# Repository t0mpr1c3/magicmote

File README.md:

Magic Mote
==========

Wireless sensor node interfacing low-power [MSP430G2553 microcontroller]("http://www.ti.com/product/msp430g2553") with [Nordic NRF24L01+]("https://www.sparkfun.com/datasheets/Components/SMD/nRF24L01Pluss_Preliminary_Product_Specification_v1_0.pdf") 2.4 GHz RF module.

Layout designed for easy compatibility with [msprf24]("https://github.com/spirilis/msprf24") and [Enrf24]("https://github.com/spirilis/Enrf24") libraries by Spirilis.

Blog post: [http://smokedprojects.blogspot.com/2017/03/magic-mote-msp430g2553-wireless-sensor.html](http://smokedprojects.blogspot.com/2017/03/magic-mote-msp430g2553-wireless-sensor.html)

Features
--------

* Unregulated power input from 2xAA or CR2032 Lithium coin cell
* 3.5mm jack socket/3 pin header with optional 2K2 pullup resistor on data line for 1-wire devices
* 4-pin header suitable for DHT22 temperature/humidity sensor
* Analogue input with low pass filter
* Tactile switch (can be mounted either side of board)
* Optional watch crystal
* Programming/serial header
* Dimensions suit panelization 24.5 x 49.00 mm footprint (2 panels on 5x5 cm)

Version history
---------------

_MO01_

First version.
Erratum: TXD and RXD labels permuted on 6-pin programming/serial header.

_MO02_

Switched TXD and RXD labels on 6-pin programming/serial header.
Moved from 3x8mm to 2x6mm watch crystal, with isolated ground plane, removed external capacitors.
Removed superfluous pulldown resistor on TST.
Changed programming/serial header to 2x3 footprint.
Changed switch to smaller SMD footprint and moved to more accessible position at side of board.

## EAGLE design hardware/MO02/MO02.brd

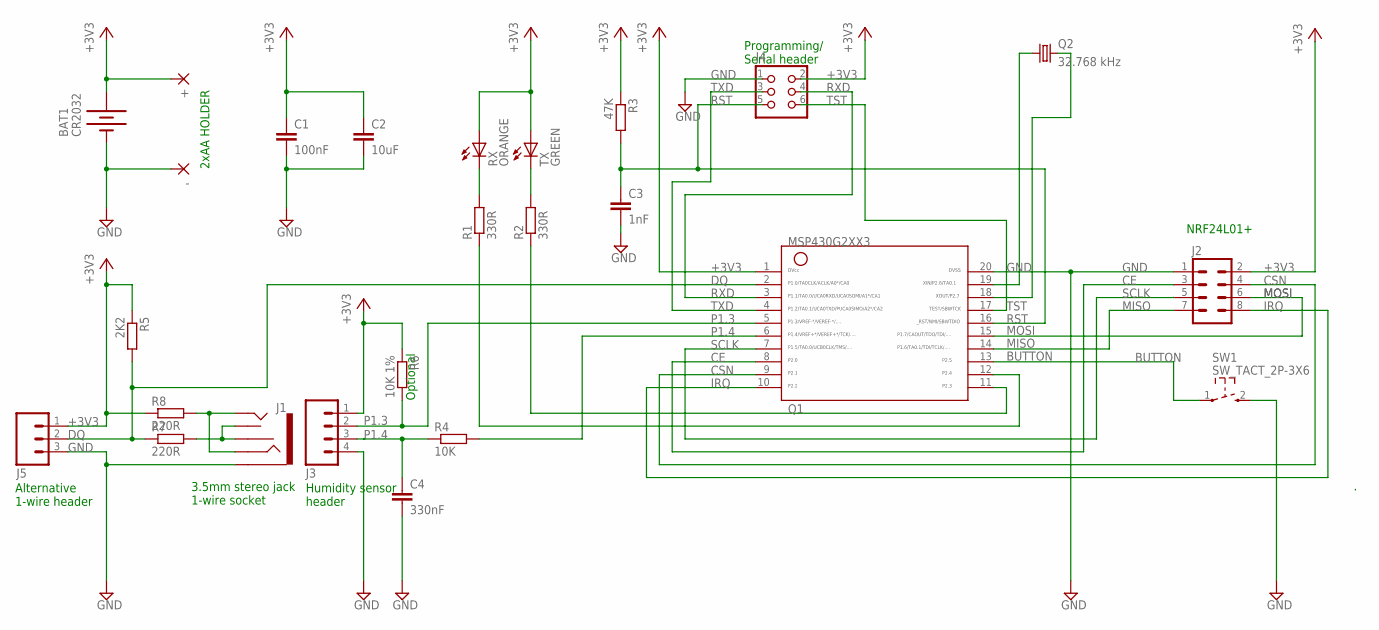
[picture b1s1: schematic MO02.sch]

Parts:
+: 2,54/1,0
-: 2,54/1,0
BAT1: CR2032; BATTCOM_20MM_PTH
C1: 100nF; C0805
C2: 10uF; C1206
C3: 1nF; C0805
C4: 330nF; C0805
J1: AUDIO-JACK2PTH; AUDIO-JACK
J2: M04X2; 2X4
J3: M04PTH; 1X04
J4: CON_HEADER_2X03-PTH; M2X3
J5: M03PTH; 1X03
Q1: G2XX3---PW20; PW20
Q2: 32.768 kHz; TC26H
R1, R2: 330R; M0805
R3: 47K; M0805
R4: 10K; M0805
R5: 2K2; M0805
R6: 10K 1%; M0805
R7, R8: 220R; M0805
RX: ORANGE; CHIPLED_0805
SW1: SW_TACT_2P-3X6; SW_TACT_3X6
TX: GREEN; CHIPLED_0805

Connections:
+3V3: +.1, BAT1.1 (+), C1.1, C2.1, J2.2, J3.1, J4.2, J5.1, Q1.1, R3.1, R5.1, R6.1, R8.1, RX.A, TX.A
BUTTON: Q1.13, SW1.1
CE: J2.3, Q1.8
CSN: J2.4, Q1.9
DQ: J5.2, Q1.2, R5.2, R7.1
GND: -.1, BAT1.2 (-), C1.2, C2.2, C3.2, C4.2, J1.SLEEVE, J2.1, J3.4, J4.1, J5.3, Q1.20, SW1.2 (3)
IRQ: J2.8, Q1.10
MISO: J2.7, Q1.14
MOSI: J2.6, Q1.15
unnamed: R2.2, TX.C
unnamed: R1.2, RX.C
unnamed: Q1.11, R2.1
unnamed: J1.RSH, J1.TSH, R7.2
unnamed: Q1.12, R1.1
unnamed: J1.RING, J1.TIP, R8.2
unnamed: C4.1, J3.3, R4.1
P1.3: J3.2, Q1.5, R6.2
P1.4: Q1.6, R4.2
P2.6: Q1.19, Q2.1
P2.7: Q1.18, Q2.2
RST: C3.1, J4.5, Q1.16, R3.2
RXD: J4.4, Q1.3
SCLK: J2.5, Q1.7
TST: J4.6, Q1.17
TXD: J4.3, Q1.4

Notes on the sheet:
3.5mm stereo jack 1-wire socket
NRF24L01+
Programming/ Serial header
Alternative 1-wire header
Humidity sensor header
Optional
2xAA HOLDER

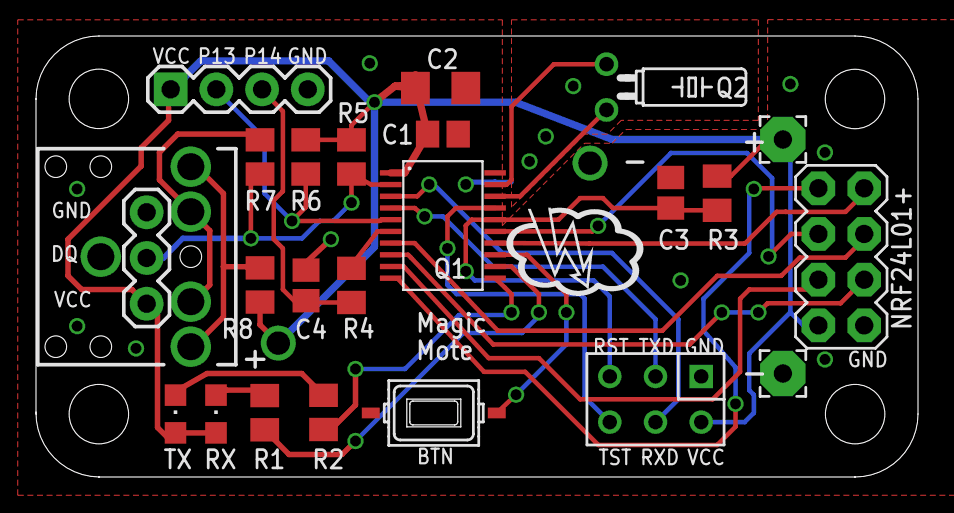
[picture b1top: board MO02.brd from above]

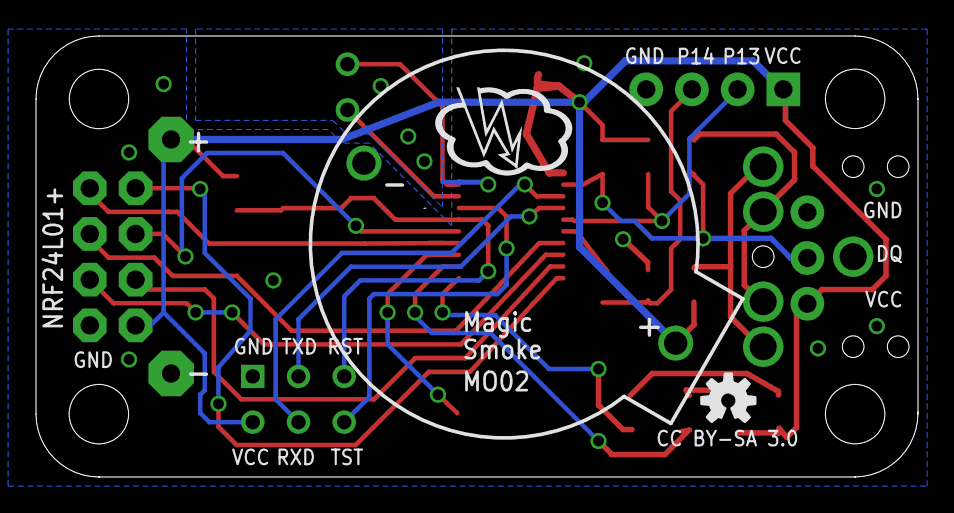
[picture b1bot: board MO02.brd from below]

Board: 2 copper layers, 49.0 x 24.5 mm, 30 parts (2 on the bottom side), 25 nets.

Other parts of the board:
U$1: OSHW-LOGO-S
U$2, U$3, U$4, U$5: STAND-OFF

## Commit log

2013-01-29 Initial commit hardware v1.0
2013-01-29 schematic .png
2013-01-29 fixed overlap of P2.5 header and coin cell holder
2013-02-01 BAT54A diode avoid charging battery
2013-02-01 moved C7
2013-02-01 VCC wire fatter
2013-02-01 rejigged a few part labels
2013-02-06 changed LEDs, added push button
2013-11-21 version WN01, first draft
2013-11-29 MO01 first draft
2013-12-05 panelized order from Elecrow
2014-01-01 revision to README
2014-01-02 version MO02
2014-01-07 2x6mm watch crystal, isolated ground plane, no external caps
2014-01-07 removed pulldown resistor on TST
2014-01-19 2x3 programming/serial header, SMD switch at side of board

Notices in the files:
hardware/MO02/MO02.brd:
CC BY-SA 3.0
parts and their libraries:
SparkFun-Connectors: Licensing: CC v3.0 Share-Alike You are welcome to use this library for commercial purposes.
